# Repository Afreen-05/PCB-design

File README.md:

# PCB-design
PCB design of STM32 and Pressure Sensor

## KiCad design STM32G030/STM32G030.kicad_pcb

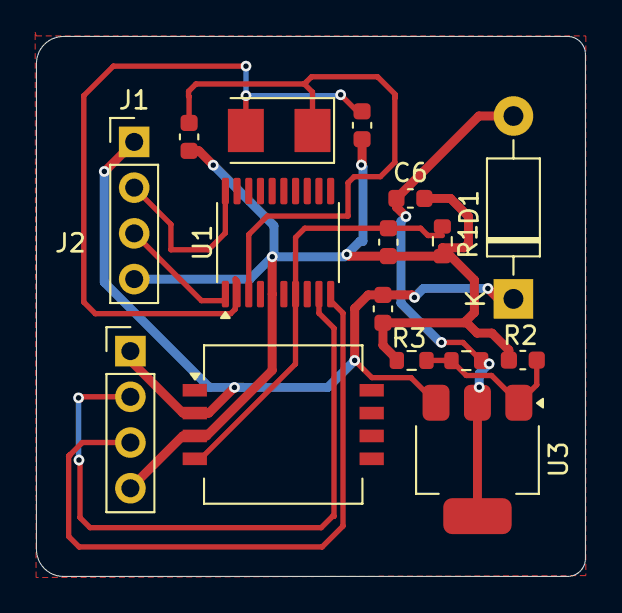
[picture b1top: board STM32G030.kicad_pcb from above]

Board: 2 copper layers, 30.5 x 30.0 mm, 16 parts (0 on the bottom side), 11 nets.

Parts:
C1: 100nf; C_0603_1608Metric
C2: 47pf; C_0603_1608Metric
C3: 10pf; C_0603_1608Metric
C4: 20pf; C_0603_1608Metric
C5: 10uF; C_0603_1608Metric
C6: 22uF; C_0603_1608Metric
D1: 1N4007; D_DO-41_SOD81_P10.16mm_Horizontal
J1, J2: Conn_01x04_Pin; PinHeader_1x04_P2.54mm_Vertical
R1: 15k; R_0603_1608Metric
R2, R3: R; R_0603_1608Metric
U1: STM32G030F6Px; TSSOP-20_4.4x6.5mm_P0.65mm
U2: MPXA6115A; Freescale_98ARH99089A
U3: AMS1117; SOT-223-3_TabPin2
Y1: 8mHz; Crystal_SMD_5032-2Pin_5.0x3.2mm

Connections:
3.3V: C6.1, D1.2 (A), R2.1, U3.2 (VO)
+5V: C1.1, D1.1 (K), J1.1, J2.1, U2.2 (Vcc), U3.3 (VI)
GND: C1.2, C2.2, C3.1, C4.1, C5.2, C6.2, J1.4, J2.4, R1.2, R3.2, U1.5 (VSS), U2.3 (GND)
unnamed: C2.1, R1.1, U1.7 (PA0), U2.4 (Vout)
unnamed: C3.2, U1.2 (PC14/PB9), Y1.2
unnamed: C4.2, U1.3 (PC15), Y1.1
unnamed: C5.1, R2.2, R3.1, U3.1 (ADJ)
UART1_RX: J1.3, U1.1 (PB7/PB8)
UART1_TX: J1.2, U1.20 (PB3/PB4/PB5/PB6)
UART2_RX: J2.3, U1.10 (PA3)
UART2_TX: J2.2, U1.9 (PA2)

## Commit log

2024-07-30 updated n
